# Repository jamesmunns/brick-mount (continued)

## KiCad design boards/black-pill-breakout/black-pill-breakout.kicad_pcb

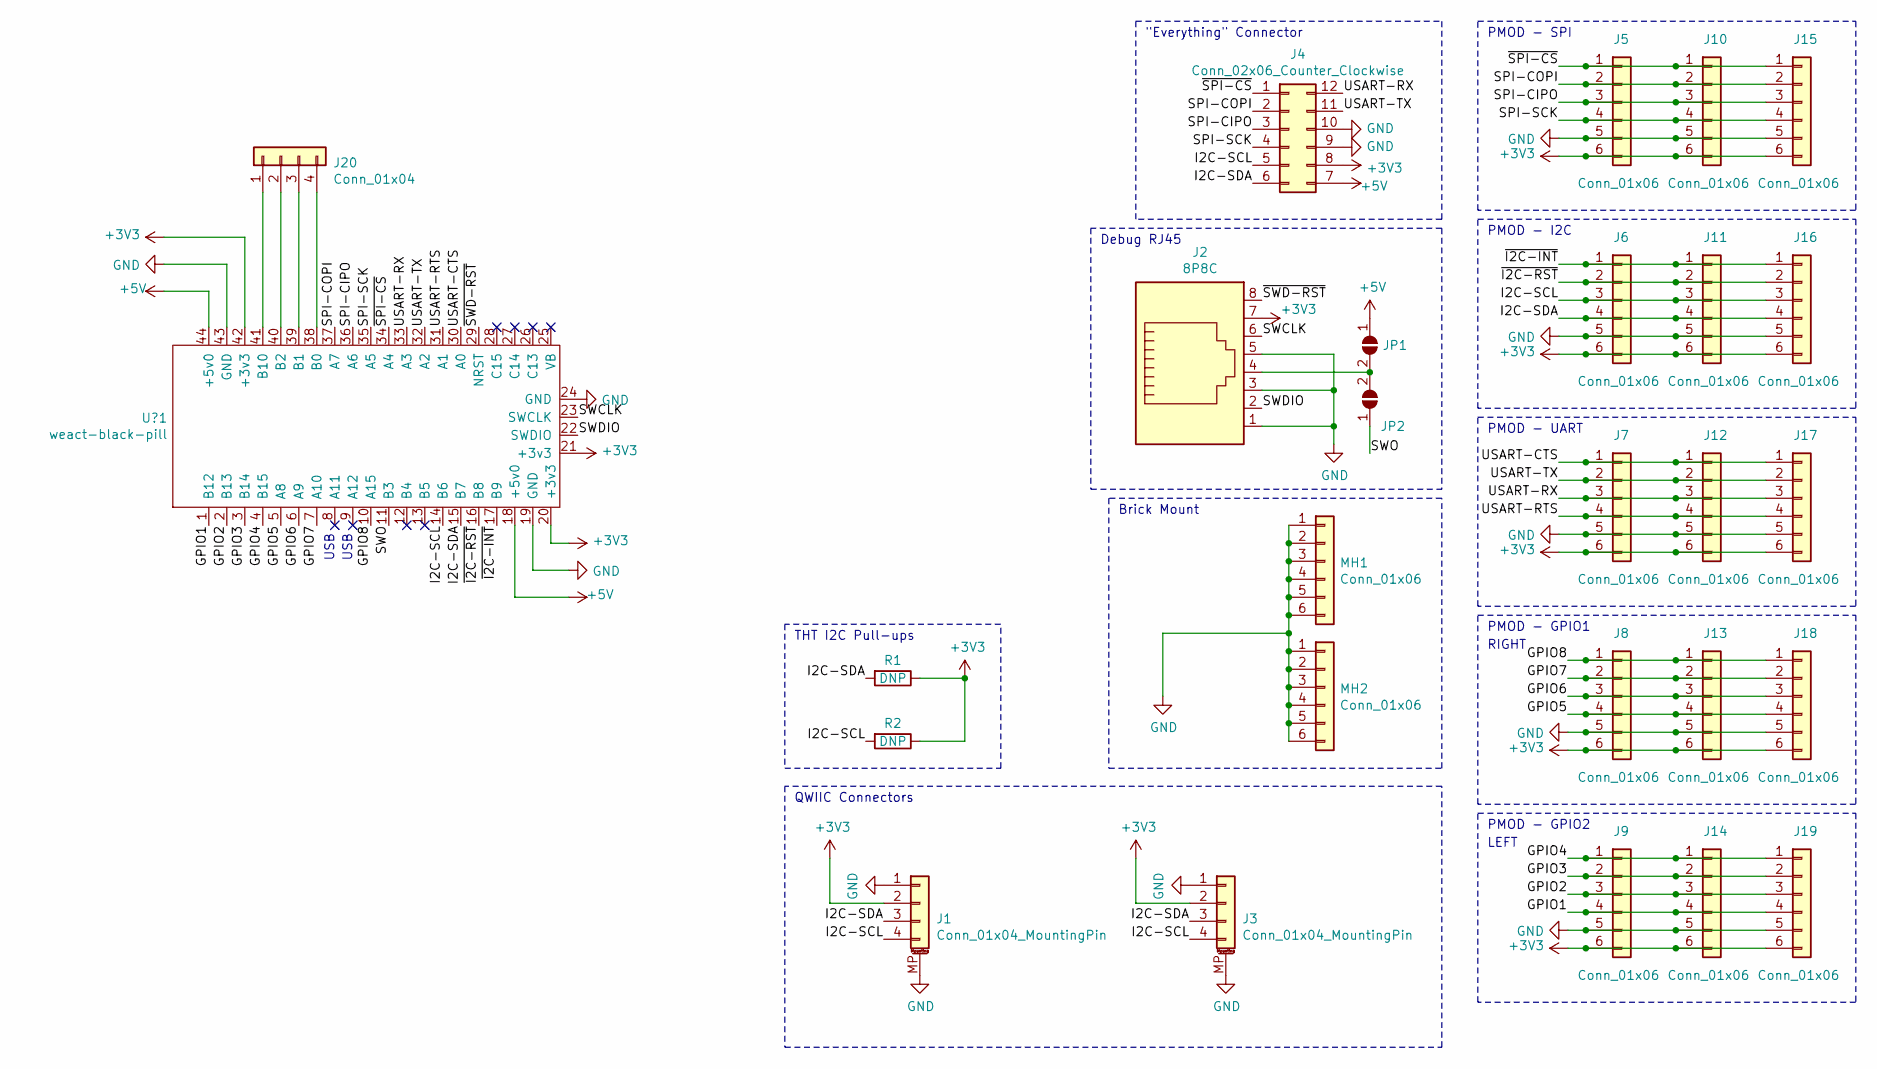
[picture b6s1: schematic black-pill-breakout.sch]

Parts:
J1, J3: Conn_01x04_MountingPin; JST_SH_SM04B-SRSS-TB_1x04-1MP_P1.00mm_Horizontal
J2: 8P8C; RJ45_Amphenol_54602-x08_Horizontal
J4: Conn_02x06_Counter_Clockwise; PinSocket_2x06_P2.54mm_Vertical
J5, J6, J7, J8, J9, J10, J11, J12, J13, J14, J15, J16, J17, J18, J19: Conn_01x06; PinSocket_1x06_P2.54mm_Vertical
J20: Conn_01x04; PinSocket_1x04_P2.54mm_Vertical
JP1, JP2: SolderJumper_2_Open; SolderJumper-2_P1.3mm_Open_TrianglePad1.0x1.5mm
MH1, MH2: Conn_01x06; brick-1x6
R1, R2: DNP; R_Axial_DIN0207_L6.3mm_D2.5mm_P10.16mm_Horizontal
U?1: weact-black-pill; weact-blackpill

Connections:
+3V3: J1.2, J2.7, J3.2, J4.8, J5.6, J6.6, J7.6, J8.6, J9.6, J10.6, J11.6, J12.6, J13.6, J14.6, J15.6, J16.6, J17.6, J18.6, J19.6, R1.1, R2.1, U?1.20 (+3v3), U?1.21 (+3v3), U?1.42 (+3v3)
+5V: J4.7, JP1.1 (A), U?1.18 (+5v0), U?1.44 (+5v0)
/GPIO1: J9.4, J14.4, J19.4, U?1.1 (B12)
/GPIO2: J9.3, J14.3, J19.3, U?1.2 (B13)
/GPIO3: J9.2, J14.2, J19.2, U?1.3 (B14)
/GPIO4: J9.1, J14.1, J19.1, U?1.4 (B15)
/GPIO5: J8.4, J13.4, J18.4, U?1.5 (A8)
/GPIO6: J8.3, J13.3, J18.3, U?1.6 (A9)
/GPIO7: J8.2, J13.2, J18.2, U?1.7 (A10)
/GPIO8: J8.1, J13.1, J18.1, U?1.10 (A15)
/I2C-SCL: J1.4, J3.4, J4.5, J6.3, J11.3, J16.3, R2.2, U?1.14 (B6)
/I2C-SDA: J1.3, J3.3, J4.6, J6.4, J11.4, J16.4, R1.2, U?1.15 (B7)
/SPI-CIPO: J4.3, J5.3, J10.3, J15.3, U?1.36 (A6)
/SPI-COPI: J4.2, J5.2, J10.2, J15.2, U?1.37 (A7)
/SPI-SCK: J4.4, J5.4, J10.4, J15.4, U?1.35 (A5)
/SWCLK: J2.6, U?1.23 (SWCLK)
/SWDIO: J2.2, U?1.22 (SWDIO)
/SWO: JP2.1 (A), U?1.11 (B3)
/USART-CTS: J7.1, J12.1, J17.1, U?1.30 (A0)
/USART-RTS: J7.4, J12.4, J17.4, U?1.31 (A1)
/USART-RX: J4.12, J7.3, J12.3, J17.3, U?1.33 (A3)
/USART-TX: J4.11, J7.2, J12.2, J17.2, U?1.32 (A2)
/~I2C-INT: J6.1, J11.1, J16.1, U?1.17 (B9)
/~I2C-RST: J6.2, J11.2, J16.2, U?1.16 (B8)
/~SPI-CS: J4.1, J5.1, J10.1, J15.1, U?1.34 (A4)
/~SWD-RST: J2.8, U?1.29 (NRST)
GND: J1.1, J1.MP (MountPin), J2.1, J2.3, J2.5, J3.1, J3.MP (MountPin), J4.9, J4.10, J5.5, J6.5, J7.5, J8.5, J9.5, J10.5, J11.5, J12.5, J13.5, J14.5, J15.5, J16.5, J17.5, J18.5, J19.5, MH1.1, MH1.2, MH1.3, MH1.4, MH1.5, MH1.6, MH2.1, MH2.2, MH2.3, MH2.4, MH2.5, MH2.6, U?1.19 (GND), U?1.24 (GND), U?1.43 (GND)
unnamed: J2.4, JP1.2 (B), JP2.2 (B)
unnamed: J20.1, U?1.41 (B10)
unnamed: J20.2, U?1.40 (B2)
unnamed: J20.3, U?1.39 (B1)
unnamed: J20.4, U?1.38 (B0)

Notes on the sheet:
PMOD - SPI
PMOD - I2C
PMOD - UART
PMOD - GPIO1
PMOD - GPIO2
"Everything" Connector
Debug RJ45
Brick Mount
QWIIC Connectors
THT I2C Pull-ups
LEFT
RIGHT
USB

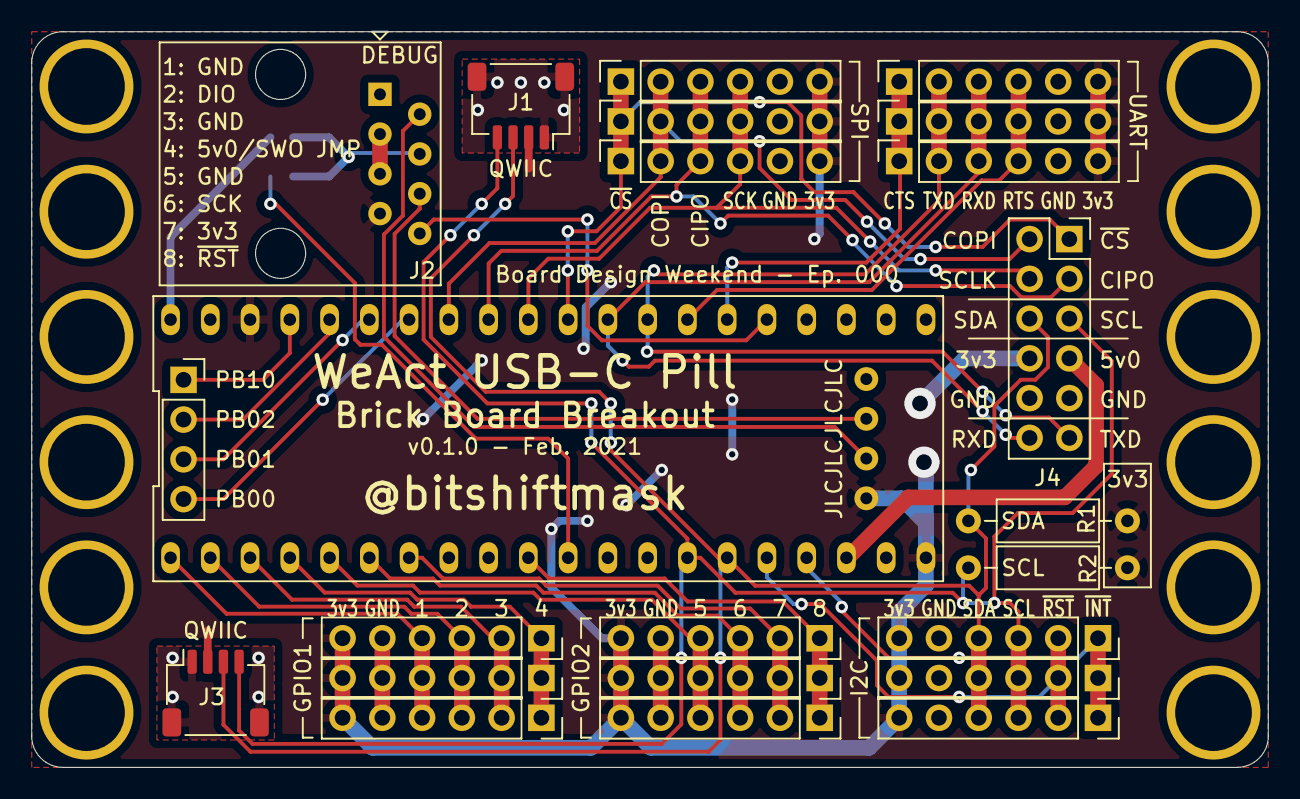
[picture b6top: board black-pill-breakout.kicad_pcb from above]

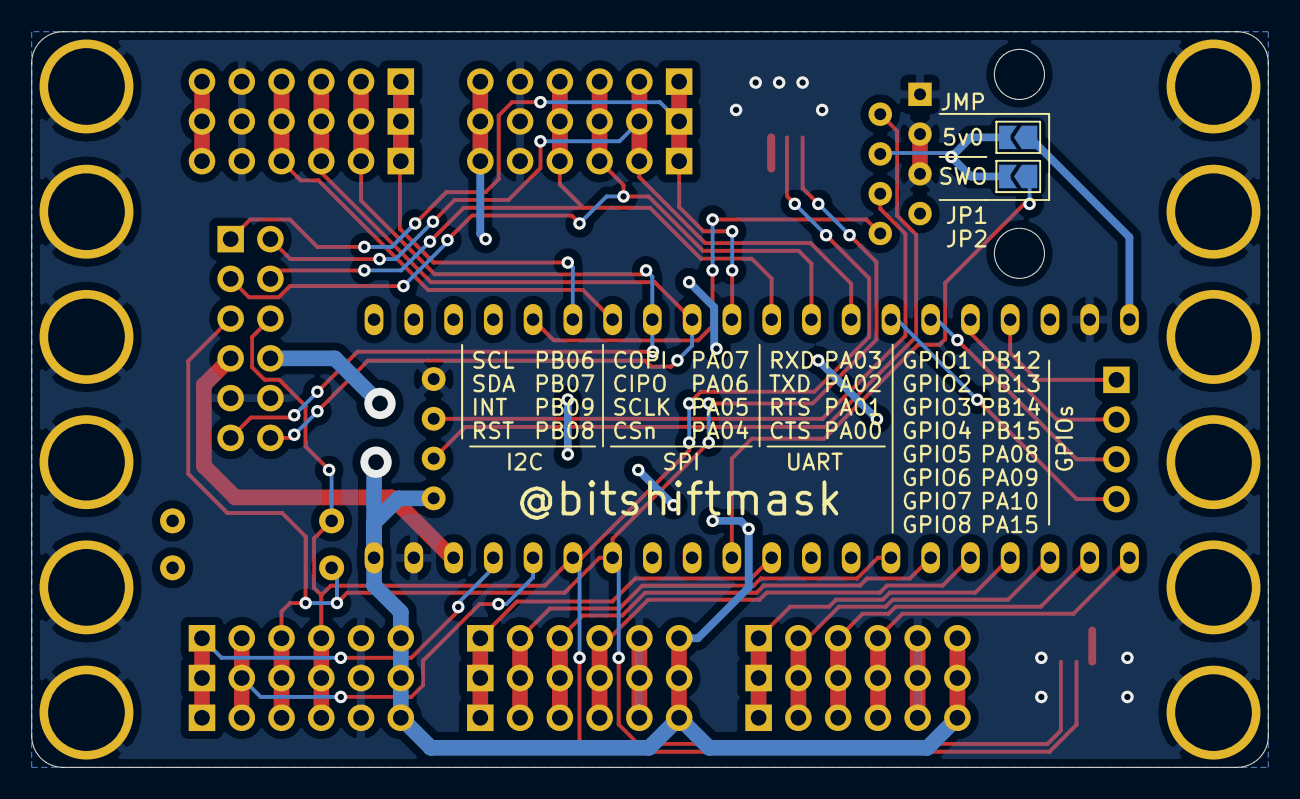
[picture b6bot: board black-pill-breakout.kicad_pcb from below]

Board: 2 copper layers, 79.0 x 47.0 mm, 27 parts (2 on the bottom side), 32 nets.

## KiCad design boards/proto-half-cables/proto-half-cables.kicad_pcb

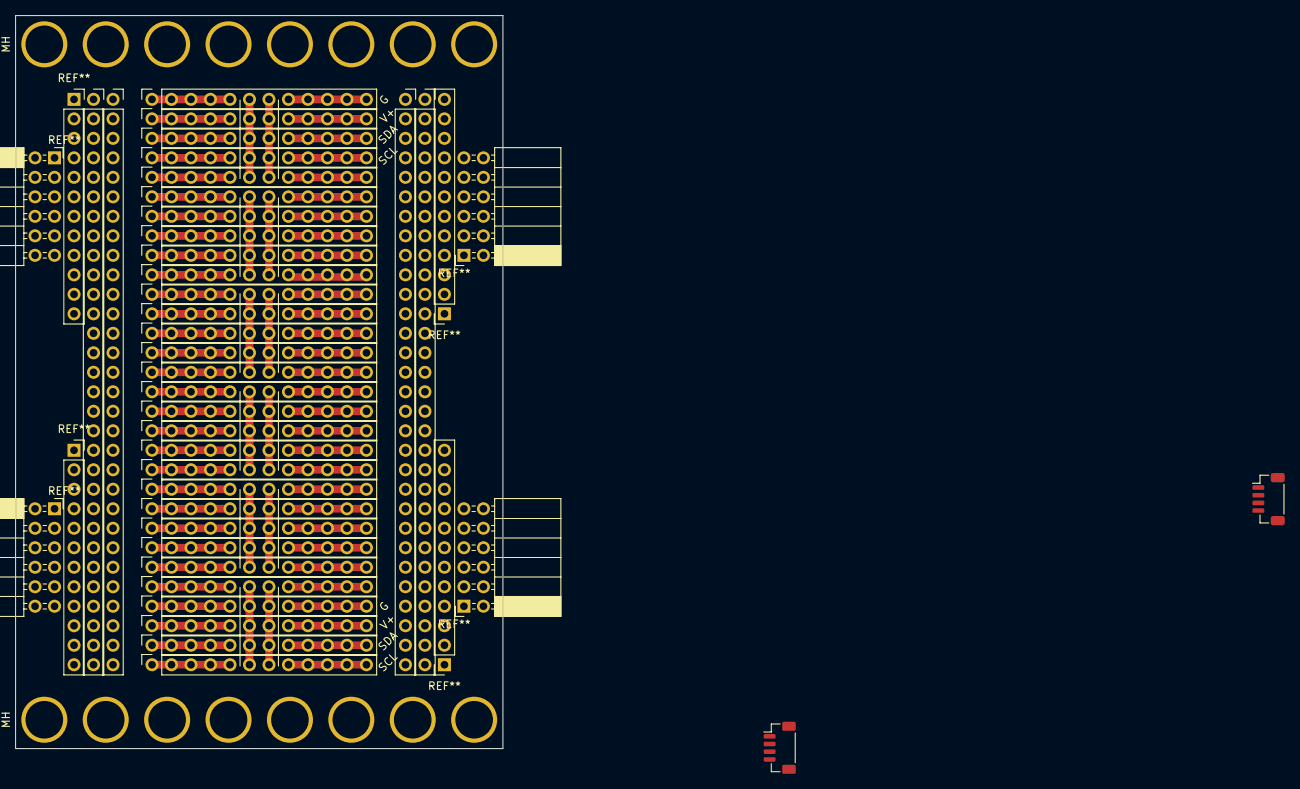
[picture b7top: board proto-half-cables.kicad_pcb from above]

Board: 2 copper layers, 63.5 x 95.5 mm, 38 parts (0 on the bottom side), 74 nets.

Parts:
J1, J2, J3, J4, J5, J6, J7, J8, J9, J10, J11, J12, J13, J14, J15, J16, J17, J18, J19, J20, J21, J22, J23, J24, J25, J26, J27, J28, J29, J30: Conn_01x12; PinSocket_1x12_P2.54mm_Vertical
J33, J33#2, J34, J34#2: Conn_01x30; PinSocket_1x30_P2.54mm_Vertical
J37, J38: Conn_01x04_MountingPin; JST_SH_BM04B-SRSS-TB_1x04-1MP_P1.00mm_Vertical
MH: brick-1x8
MH#2: brick-1x8

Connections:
/Q1-3v3: J2.8, J2.9, J2.10, J2.11, J2.12, J37.2
/Q1-GND: J1.8, J1.9, J1.10, J1.11, J1.12, J37.1, J37.MP
/Q1-SCL: J4.8, J4.9, J4.10, J4.11, J4.12, J37.4
/Q1-SDA: J3.8, J3.9, J3.10, J3.11, J3.12, J37.3
/Q2-3v3: J28.8, J28.9, J28.10, J28.11, J28.12, J38.2
/Q2-GND: J27.8, J27.9, J27.10, J27.11, J27.12, J38.1, J38.MP
/Q2-SCL: J30.8, J30.9, J30.10, J30.11, J30.12, J38.4
/Q2-SDA: J29.8, J29.9, J29.10, J29.11, J29.12, J38.3
unnamed: J1.1, J1.2, J1.3, J1.4, J1.5
unnamed: J1.6, J2.6, J3.6, J4.6, J5.6
unnamed: J1.7, J2.7, J3.7, J4.7, J5.7
unnamed: J2.1, J2.2, J2.3, J2.4, J2.5
unnamed: J3.1, J3.2, J3.3, J3.4, J3.5
unnamed: J4.1, J4.2, J4.3, J4.4, J4.5
unnamed: J5.1, J5.2, J5.3, J5.4, J5.5
unnamed: J5.8, J5.9, J5.10, J5.11, J5.12
unnamed: J6.1, J6.2, J6.3, J6.4, J6.5
unnamed: J6.8, J6.9, J6.10, J6.11, J6.12
unnamed: J7.1, J7.2, J7.3, J7.4, J7.5
unnamed: J7.8, J7.9, J7.10, J7.11, J7.12
unnamed: J8.1, J8.2, J8.3, J8.4, J8.5
unnamed: J8.8, J8.9, J8.10, J8.11, J8.12
unnamed: J9.1, J9.2, J9.3, J9.4, J9.5
unnamed: J9.8, J9.9, J9.10, J9.11, J9.12
unnamed: J10.1, J10.2, J10.3, J10.4, J10.5
unnamed: J6.6, J7.6, J8.6, J9.6, J10.6
unnamed: J6.7, J7.7, J8.7, J9.7, J10.7
unnamed: J10.8, J10.9, J10.10, J10.11, J10.12
unnamed: J11.1, J11.2, J11.3, J11.4, J11.5
unnamed: J11.6, J12.6, J13.6, J14.6, J15.6
unnamed: J11.7, J12.7, J13.7, J14.7, J15.7
unnamed: J11.8, J11.9, J11.10, J11.11, J11.12
unnamed: J12.1, J12.2, J12.3, J12.4, J12.5
unnamed: J12.8, J12.9, J12.10, J12.11, J12.12
unnamed: J13.1, J13.2, J13.3, J13.4, J13.5
unnamed: J13.8, J13.9, J13.10, J13.11, J13.12
unnamed: J14.1, J14.2, J14.3, J14.4, J14.5
unnamed: J14.8, J14.9, J14.10, J14.11, J14.12
unnamed: J15.1, J15.2, J15.3, J15.4, J15.5
unnamed: J15.8, J15.9, J15.10, J15.11, J15.12
unnamed: J16.1, J16.2, J16.3, J16.4, J16.5
unnamed: J16.6, J17.6, J18.6, J19.6, J20.6
unnamed: J16.7, J17.7, J18.7, J19.7, J20.7
unnamed: J16.8, J16.9, J16.10, J16.11, J16.12
unnamed: J17.1, J17.2, J17.3, J17.4, J17.5
unnamed: J17.8, J17.9, J17.10, J17.11, J17.12
unnamed: J18.1, J18.2, J18.3, J18.4, J18.5
unnamed: J18.8, J18.9, J18.10, J18.11, J18.12
unnamed: J19.1, J19.2, J19.3, J19.4, J19.5
unnamed: J19.8, J19.9, J19.10, J19.11, J19.12
unnamed: J20.1, J20.2, J20.3, J20.4, J20.5
unnamed: J20.8, J20.9, J20.10, J20.11, J20.12
unnamed: J21.1, J21.2, J21.3, J21.4, J21.5
unnamed: J21.6, J22.6, J23.6, J24.6, J25.6
unnamed: J21.7, J22.7, J23.7, J24.7, J25.7
unnamed: J21.8, J21.9, J21.10, J21.11, J21.12
unnamed: J22.1, J22.2, J22.3, J22.4, J22.5
unnamed: J22.8, J22.9, J22.10, J22.11, J22.12
unnamed: J23.1, J23.2, J23.3, J23.4, J23.5
unnamed: J23.8, J23.9, J23.10, J23.11, J23.12
unnamed: J24.1, J24.2, J24.3, J24.4, J24.5
unnamed: J24.8, J24.9, J24.10, J24.11, J24.12
unnamed: J25.1, J25.2, J25.3, J25.4, J25.5
unnamed: J25.8, J25.9, J25.10, J25.11, J25.12
unnamed: J26.1, J26.2, J26.3, J26.4, J26.5
unnamed: J26.6, J27.6, J28.6, J29.6, J30.6
unnamed: J26.7, J27.7, J28.7, J29.7, J30.7
unnamed: J26.8, J26.9, J26.10, J26.11, J26.12
unnamed: J27.1, J27.2, J27.3, J27.4, J27.5
unnamed: J28.1, J28.2, J28.3, J28.4, J28.5
unnamed: J29.1, J29.2, J29.3, J29.4, J29.5
unnamed: J30.1, J30.2, J30.3, J30.4, J30.5
unnamed: J33#2.1, J33#2.2, J33#2.3, J33#2.4, J33#2.5, J33#2.6, J33#2.7, J33#2.8, J33#2.9, J33#2.10, J33#2.11, J33#2.12, J33#2.13, J33#2.14, J33#2.15, J33#2.16, J33#2.17, J33#2.18, J33#2.19, J33#2.20, J33#2.21, J33#2.22, J33#2.23, J33#2.24, J33#2.25, J33#2.26, J33#2.27, J33#2.28, J33#2.29, J33#2.30
unnamed: J34#2.1, J34#2.2, J34#2.3, J34#2.4, J34#2.5, J34#2.6, J34#2.7, J34#2.8, J34#2.9, J34#2.10, J34#2.11, J34#2.12, J34#2.13, J34#2.14, J34#2.15, J34#2.16, J34#2.17, J34#2.18, J34#2.19, J34#2.20, J34#2.21, J34#2.22, J34#2.23, J34#2.24, J34#2.25, J34#2.26, J34#2.27, J34#2.28, J34#2.29, J34#2.30

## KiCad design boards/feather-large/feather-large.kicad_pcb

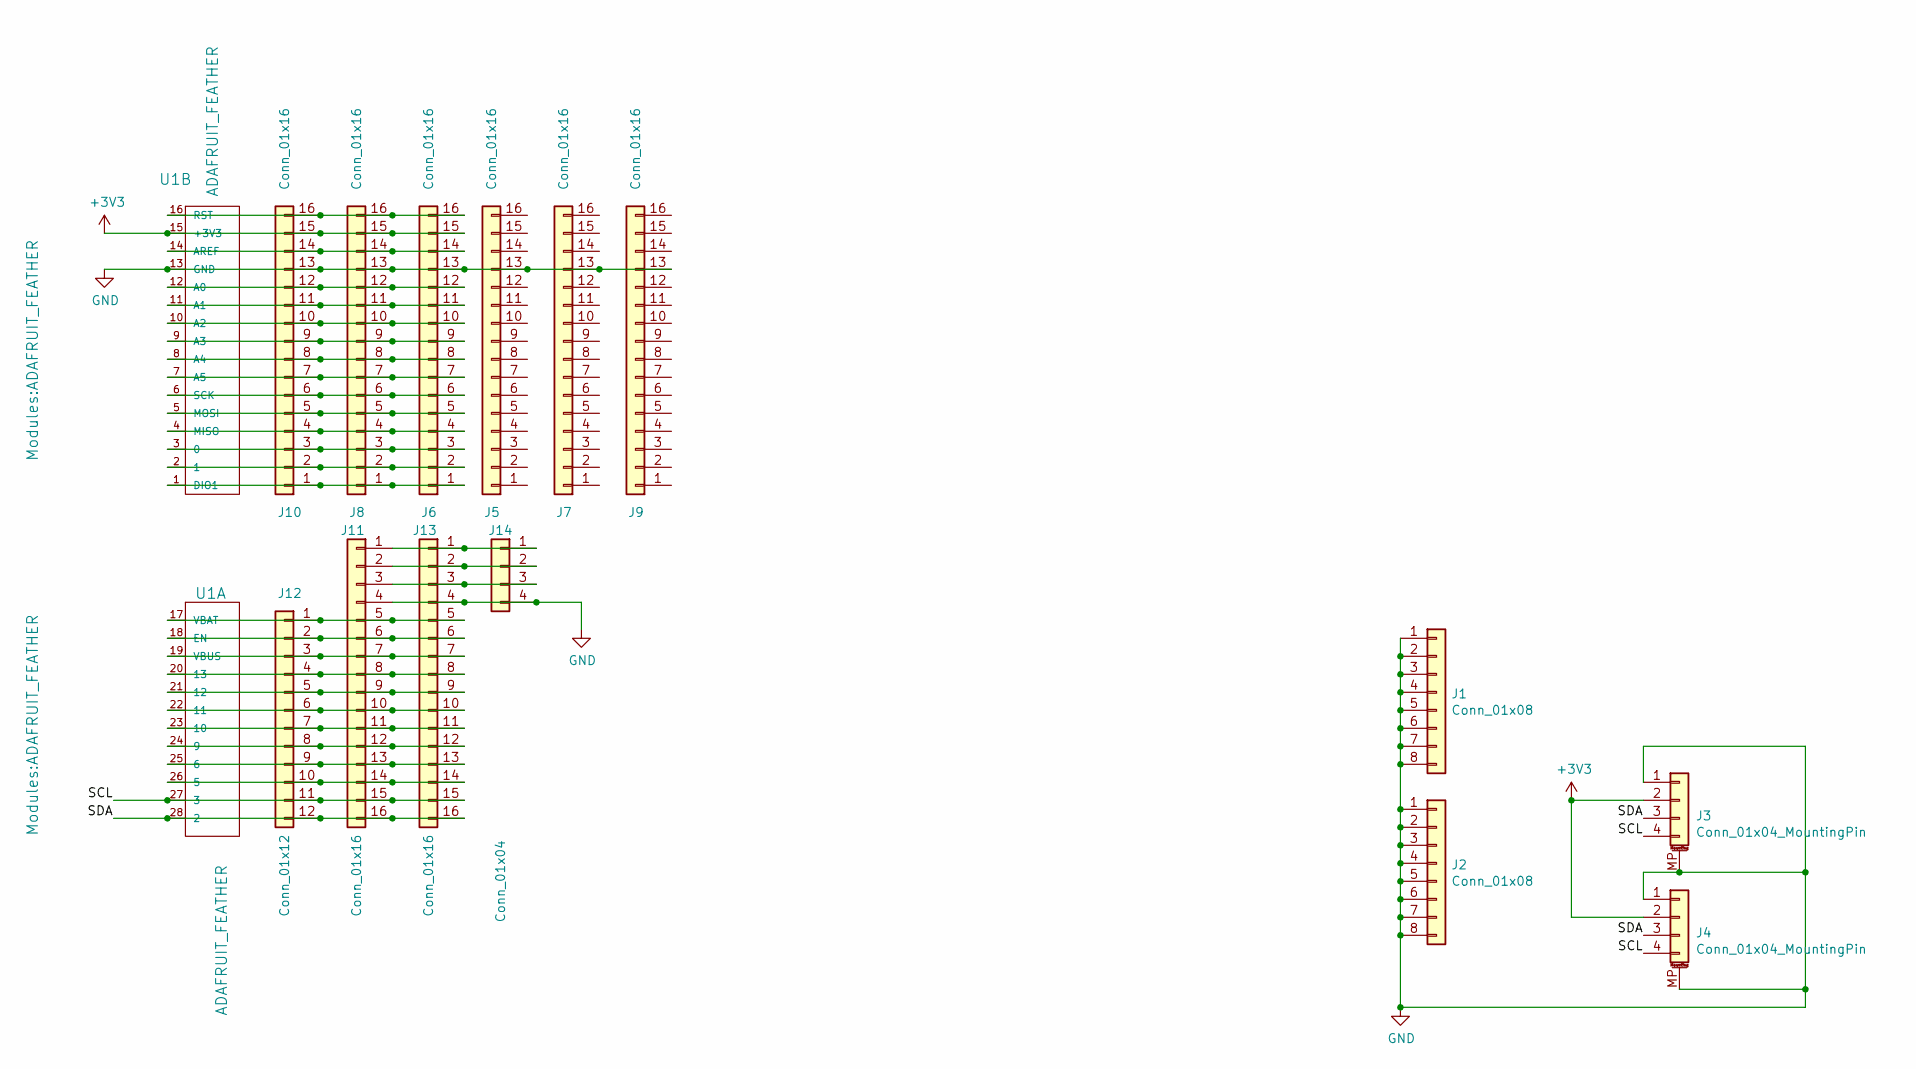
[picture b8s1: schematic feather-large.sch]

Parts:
J1, J2: Conn_01x08; brick-1x8
J3, J4: Conn_01x04_MountingPin; JST_SH_SM04B-SRSS-TB_1x04-1MP_P1.00mm_Horizontal
J5, J6, J7, J8, J9, J10, J11, J13: Conn_01x16; PinSocket_1x16_P2.54mm_Vertical
J12: Conn_01x12; PinSocket_1x12_P2.54mm_Vertical
J14: Conn_01x04; PinSocket_1x04_P2.54mm_Vertical
U1: ADAFRUIT_FEATHER

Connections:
+3V3: J3.2, J4.2, J6.15, J8.15, J10.15, U1.15 (+3V3)
/SCL: J3.4, J4.4, J11.15, J12.11, J13.15, U1.27 (3)
/SDA: J3.3, J4.3, J11.16, J12.12, J13.16, U1.28 (2)
GND: J1.1, J1.2, J1.3, J1.4, J1.5, J1.6, J1.7, J1.8, J2.1, J2.2, J2.3, J2.4, J2.5, J2.6, J2.7, J2.8, J3.1, J3.MP (MountPin), J4.1, J4.MP (MountPin), J5.13, J6.13, J7.13, J8.13, J9.13, J10.13, J11.4, J13.4, J14.4, U1.13 (GND)
unnamed: J6.1, J8.1, J10.1, U1.1 (DIO1)
unnamed: J6.2, J8.2, J10.2, U1.2 (1)
unnamed: J6.3, J8.3, J10.3, U1.3 (0)
unnamed: J6.4, J8.4, J10.4, U1.4 (MISO)
unnamed: J6.5, J8.5, J10.5, U1.5 (MOSI)
unnamed: J6.6, J8.6, J10.6, U1.6 (SCK)
unnamed: J6.7, J8.7, J10.7, U1.7 (A5)
unnamed: J6.8, J8.8, J10.8, U1.8 (A4)
unnamed: J6.9, J8.9, J10.9, U1.9 (A3)
unnamed: J6.10, J8.10, J10.10, U1.10 (A2)
unnamed: J6.11, J8.11, J10.11, U1.11 (A1)
unnamed: J6.12, J8.12, J10.12, U1.12 (A0)
unnamed: J6.14, J8.14, J10.14, U1.14 (AREF)
unnamed: J6.16, J8.16, J10.16, U1.16 (RST)
unnamed: J11.1, J13.1, J14.1
unnamed: J11.2, J13.2, J14.2
unnamed: J11.3, J13.3, J14.3
unnamed: J11.5, J12.1, J13.5, U1.17 (VBAT)
unnamed: J11.6, J12.2, J13.6, U1.18 (EN)
unnamed: J11.7, J12.3, J13.7, U1.19 (VBUS)
unnamed: J11.8, J12.4, J13.8, U1.20 (13)
unnamed: J11.9, J12.5, J13.9, U1.21 (12)
unnamed: J11.10, J12.6, J13.10, U1.22 (11)
unnamed: J11.11, J12.7, J13.11, U1.23 (10)
unnamed: J11.12, J12.8, J13.12, U1.24 (9)
unnamed: J11.13, J12.9, J13.13, U1.25 (6)
unnamed: J11.14, J12.10, J13.14, U1.26 (5)

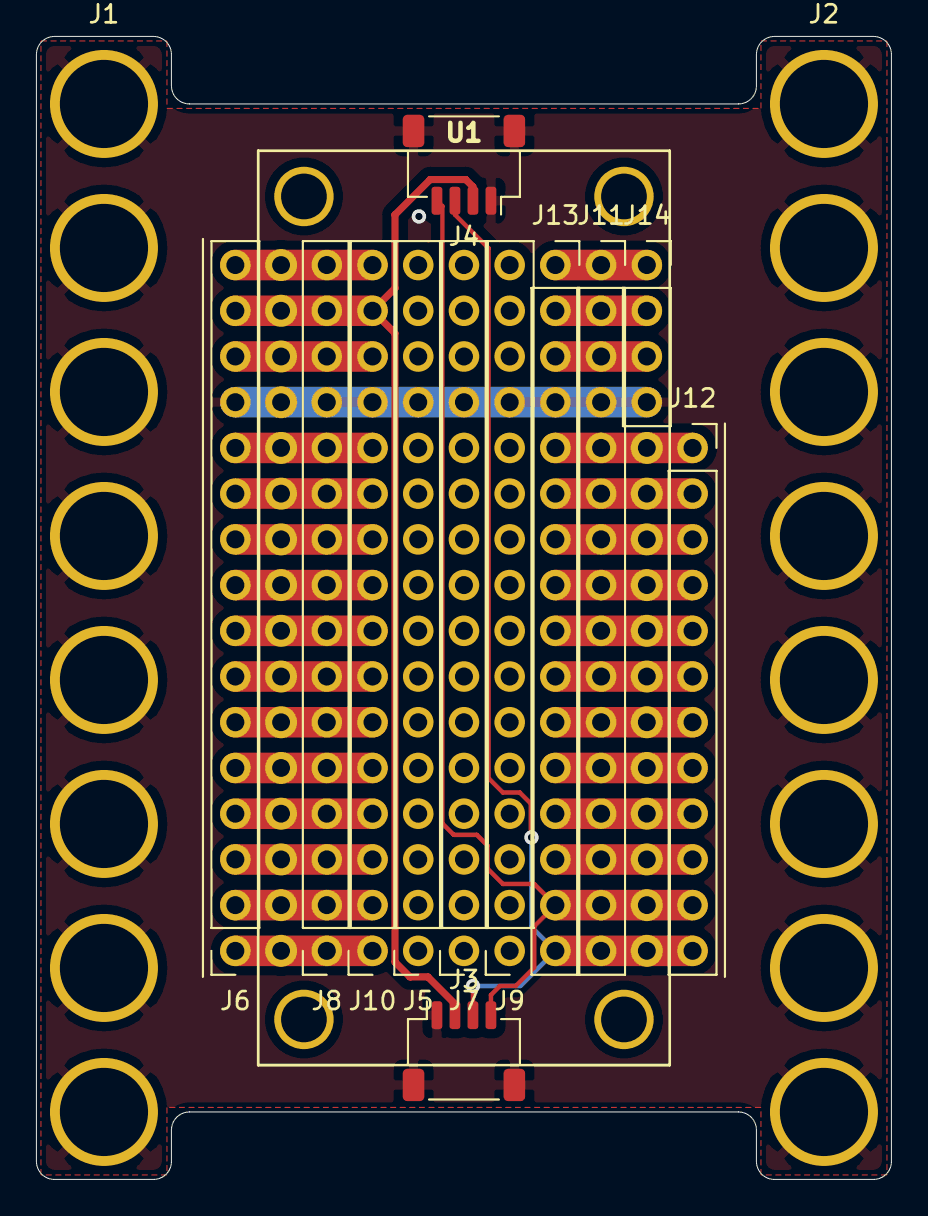
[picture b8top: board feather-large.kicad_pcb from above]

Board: 2 copper layers, 47.5 x 63.5 mm, 15 parts (0 on the bottom side), 31 nets.

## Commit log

2021-01-19 Add new boards
    These were ordered on 2021-01-19.
2021-01-21 Start to fix the proto board connectors.
    Half board is fixed, quarter board requires reducing the length of a couple
    of the connectors, namely the power rails and the top-right proto line.
2021-01-23 Add reform as a submodule
2021-01-24 Pretty much done, outside of silkscreen
2021-01-24 Update schematic
2021-01-24 Finalize choc-keypad
2021-01-24 Fix some silkscreen, update to v0.1.1 for non-X2 re-export
2021-02-28 Pre-stream setup
2021-02-28 First idea
2021-02-28 Layout idea #2
2021-02-28 Done routing, pre-silkscreen
2021-02-28 Board Complete - Pre-Export
2021-03-07 I don't know what this branch is
2021-03-08 Work
2021-03-08 Re-place, pre-route
    Trying to keep the 5V low, and the center path clear
2021-03-08 Dead end-ish, going to re-wipe and retry
2021-03-08 Gunna bail.
2021-03-08 About to give up again
2021-03-08 Everything but the LEDs
2021-03-08 seems done?
2021-03-08 Pre-silk
2021-03-09 Pre-order
2021-03-09 More cleanup
2021-03-09 Pre-export
2021-03-23 Add recent projects
2021-03-26 putzing
2022-03-27 Window dressing
2022-04-22 Add char board (and probably some other stuff)
